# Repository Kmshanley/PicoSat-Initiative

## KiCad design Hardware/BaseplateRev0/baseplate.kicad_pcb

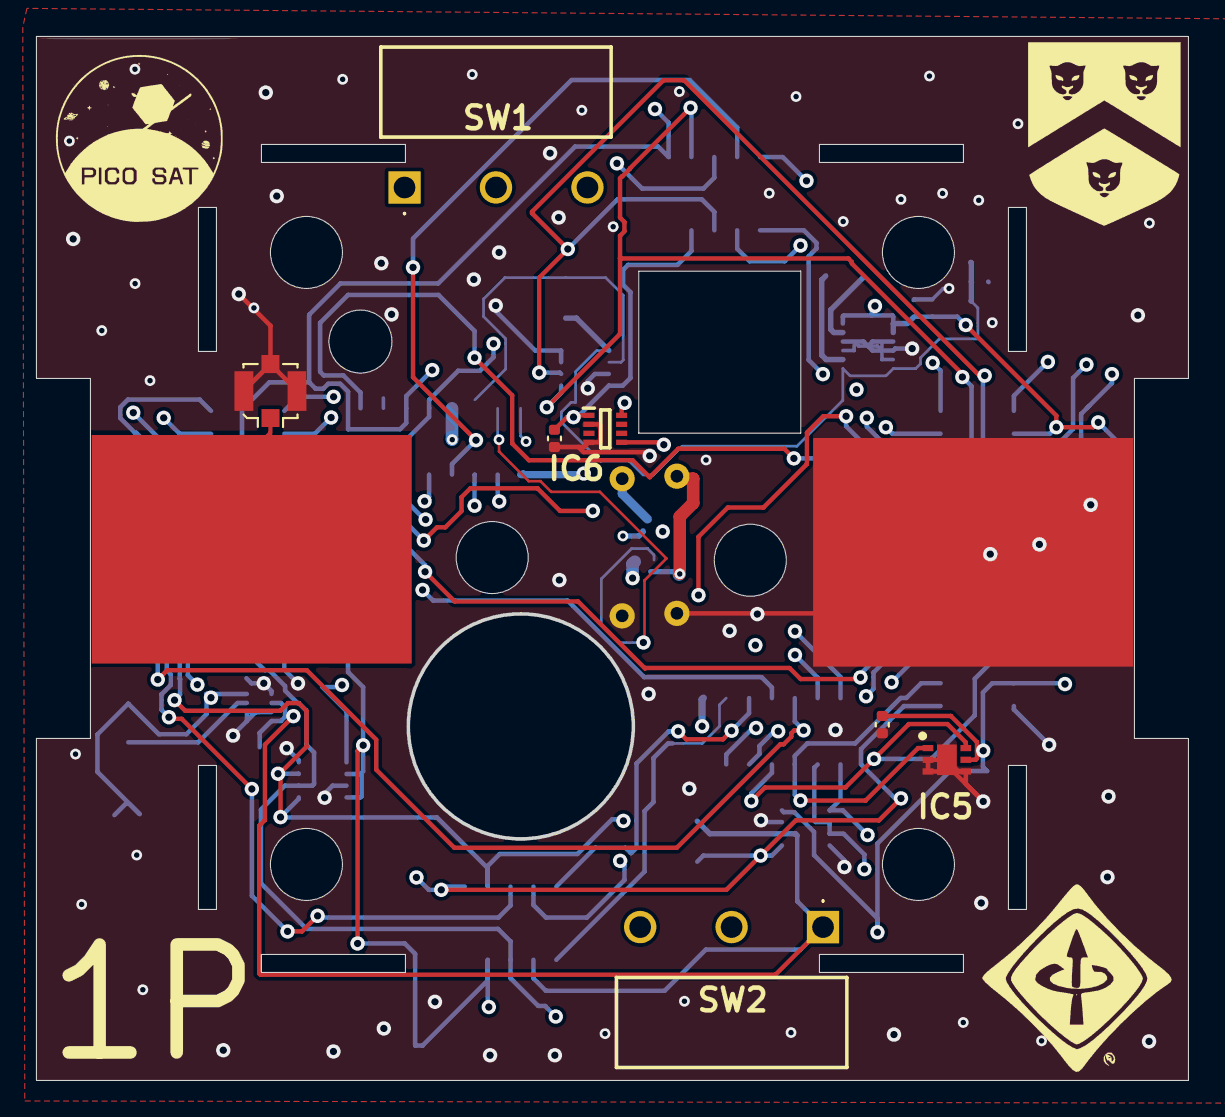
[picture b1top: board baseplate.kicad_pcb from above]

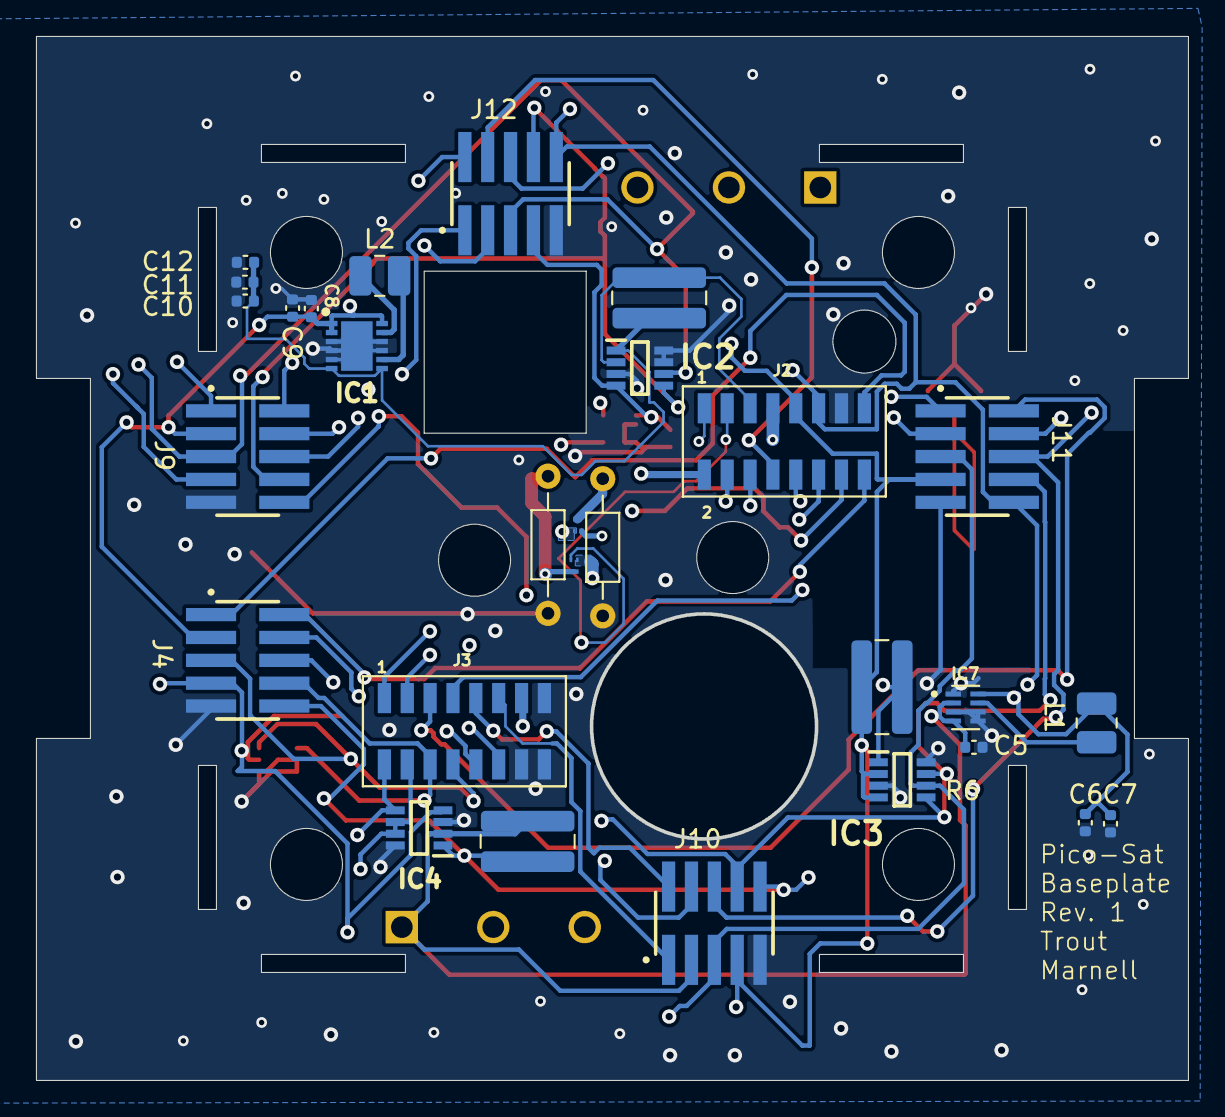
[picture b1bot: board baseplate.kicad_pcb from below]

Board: 4 copper layers, 64.0 x 58.0 mm, 38 parts (29 on the bottom side), 36 nets.

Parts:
C5: 4.7uF; C_0402_1005Metric
C6, C9, C10, C11: 10uF; C_0402_1005Metric
C7, C8, C12: 1uF; C_0402_1005Metric
C13, C14: 0.1uF; C_0402_1005Metric
IC1: RP604K331A-TR; SON50P270X300X60-13N
IC2, IC3, IC4: INA236AIDDFR; SOP65P280X110-8N
IC5: TMP117MAIDRVR; SON65P200X200X80-7N
IC6: OPT4048DTSR; SOTFL50P190X60-8N
IC7: TPS62840DLCR; SON50P200X150X100-8N
J1: Conn_Coaxial; U.FL_Molex_MCRF_73412-0110_Vertical
J2, J3: FLE-108-01-XX-DV
J4, J9, J10, J11, J12: FTSH-105-XX-X-DV; SAMTEC_FTSH-105-XX-X-DV
L1, L2: 2.2uH; L_1008_2520Metric
Q1, Q2: 2N7002; Transistor for baseplate
R1, R2: R_Small_US; R_Axial_DIN0204_L3.6mm_D1.6mm_P7.62mm_Horizontal
R5, R6, R7: 20m; R_1020_2550Metric
SW1, SW2: SW_SPDT; D2FL2A1
U1: (no value)
U2: antenna

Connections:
1.8V: C13.2, C14.2, IC2.4 (VS), IC3.2 (IN-), IC3.4 (VS), IC4.4 (VS), IC5.5 (V+), IC6.1 (VDD), J2.9, J4.07, J9.07, J10.07, J11.07, J12.07, R6.2
1V8 MEASURE: C6.1, C7.1, IC3.1 (IN+), IC7.8 (VOS), L1.2, R6.1
3.3V: IC2.2 (IN-), J2.5, R5.2
3V3 MEASURE: C10.1, C11.1, C12.1, IC1.6 (VFB), IC1.7 (VOUT), IC2.1 (IN+), R5.1
Battery +: C5.1, C8.2, C9.2, IC1.1 (AVIN), IC1.2 (CE), IC1.12 (PVIN), IC4.2 (IN-), IC7.2 (VIN), IC7.4 (EN), J2.2, J3.13, J4.03, J9.03, J10.03, J11.03, J12.03, Q1.2 (S), Q2.2 (S), R7.2, SW1.1 (A), SW2.1 (A)
DRV ENABLE 1: J2.14, J9.04
DRV ENABLE 2: J2.12, J10.04
DRV ENABLE 3: J2.10, J11.04
DRV ENABLE 4: J2.8, J12.04
DRV ENABLE 5: J2.6, J4.04
GND: C5.2, C6.2, C7.2, C8.1, C9.1, C10.2, C11.2, C12.2, C13.1, C14.1, IC1.3 (PGND_1), IC1.4 (PGND_2), IC1.5 (AGND), IC1.9 (PGND_3), IC1.10 (PGND_4), IC1.13 (EP), IC2.3 (GND), IC2.7 (A0), IC2.8 (ALERT), IC3.3 (GND), IC3.8 (ALERT), IC4.3 (GND), IC4.8 (ALERT), IC5.2 (GND), IC5.3 (ALERT), IC5.4 (ADD0), IC5.7 (EP), IC6.2 (ADDR), IC6.4 (GND), IC7.1 (GND), IC7.3 (MODE), IC7.5 (VSET), IC7.6 (STOP), J1.2 (Ext), J2.13, J3.14, J3.15, J3.16, J4.09, J9.09, J10.09, J11.09, J12.09, R1.2, R2.2, U1.1 (RF_IN)
MCU ENABLE 1: J2.3, Q1.1 (G)
MCU ENABLE 2: J2.1, Q2.1 (G)
MPPT ENABLE: J2.4, J4.06, J9.06, J10.06, J11.06, J12.06
unnamed: IC1.8 (BOLX), L2.2
unnamed: IC1.11 (BULX), L2.1
unnamed: IC7.7 (SW), L1.1
unnamed: Q2.3 (D), R1.1
unnamed: Q1.3 (D), R2.1
PWM1(1): J3.10, J9.01
PWM1(2): J3.11, J10.01
PWM1(3): J3.7, J11.01
PWM1(4): J3.3, J12.01
PWM1(5): J2.15, J4.01
PWM2(1): J3.12, J9.02
PWM2(2): J3.9, J10.02
PWM2(3): J3.5, J11.02
PWM2(4): J3.1, J12.02
PWM2(5): J2.16, J4.02
RF ANTENNA: J1.1 (In), U2.1 (RF_IN)
SCL(1): IC2.5 (SCL), IC3.5 (SCL), IC3.7 (A0), IC4.5 (SCL), J3.2, J9.08, J10.08, J11.08, J12.08
SCL(2): IC5.1 (SCL), IC6.5 (SCL), J3.6, J4.08
SDA(1): IC2.6 (SDA), IC3.6 (SDA), IC4.6 (SDA), IC4.7 (A0), J3.4, J9.05, J10.05, J11.05, J12.05
SDA(2): IC5.6 (SDA), IC6.8 (SDA), J3.8, J4.05
VBAT+: J2.7, SW1.2 (B), SW2.2 (B)
VMPPT: IC4.1 (IN+), J2.11, J4.10, J9.10, J10.10, J11.10, J12.10, R7.1

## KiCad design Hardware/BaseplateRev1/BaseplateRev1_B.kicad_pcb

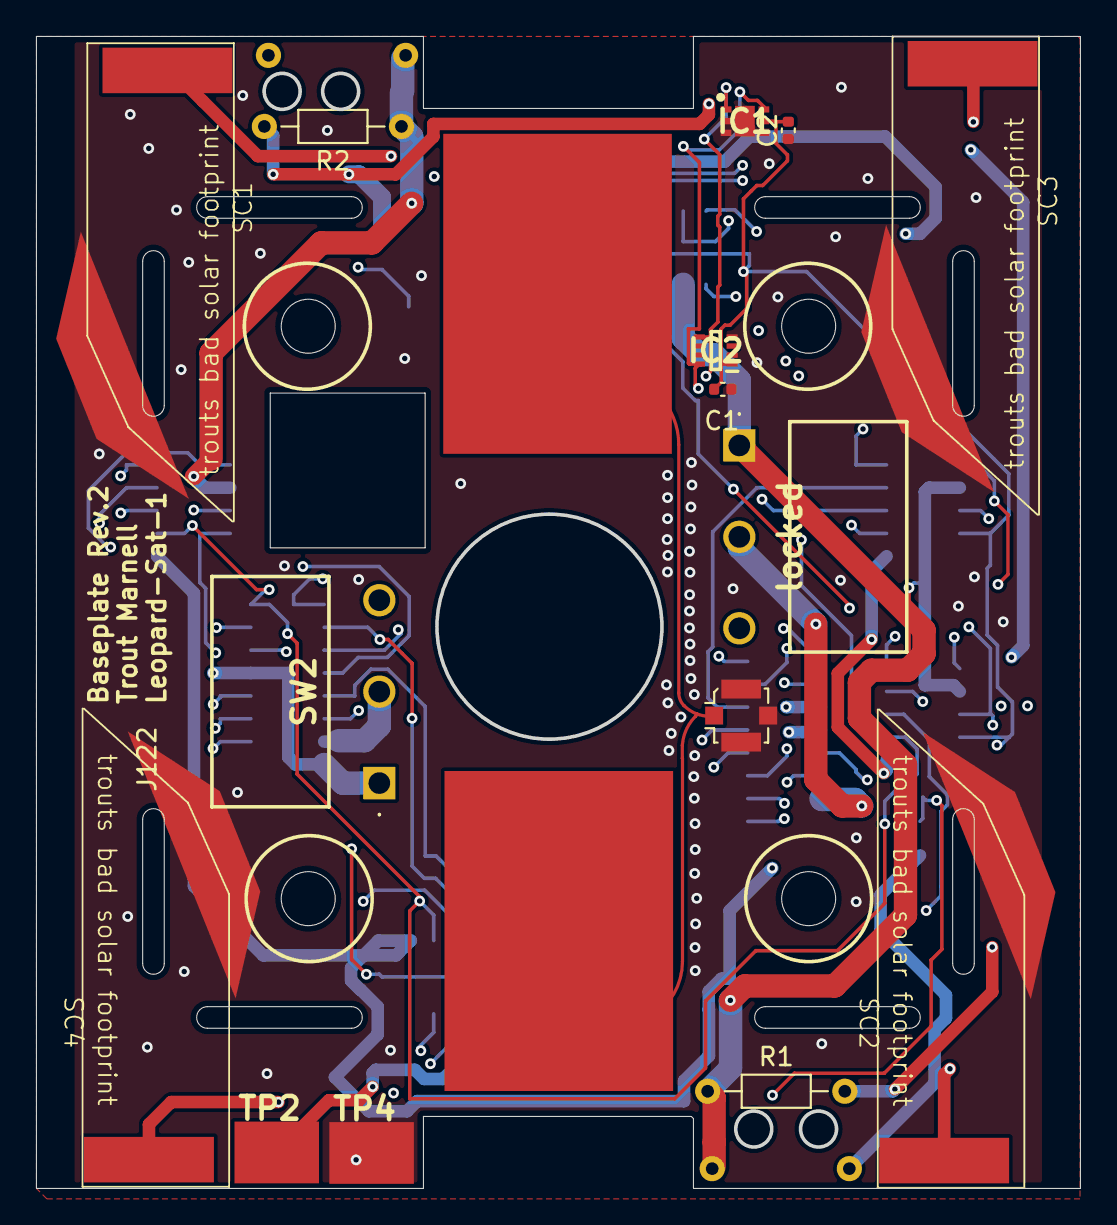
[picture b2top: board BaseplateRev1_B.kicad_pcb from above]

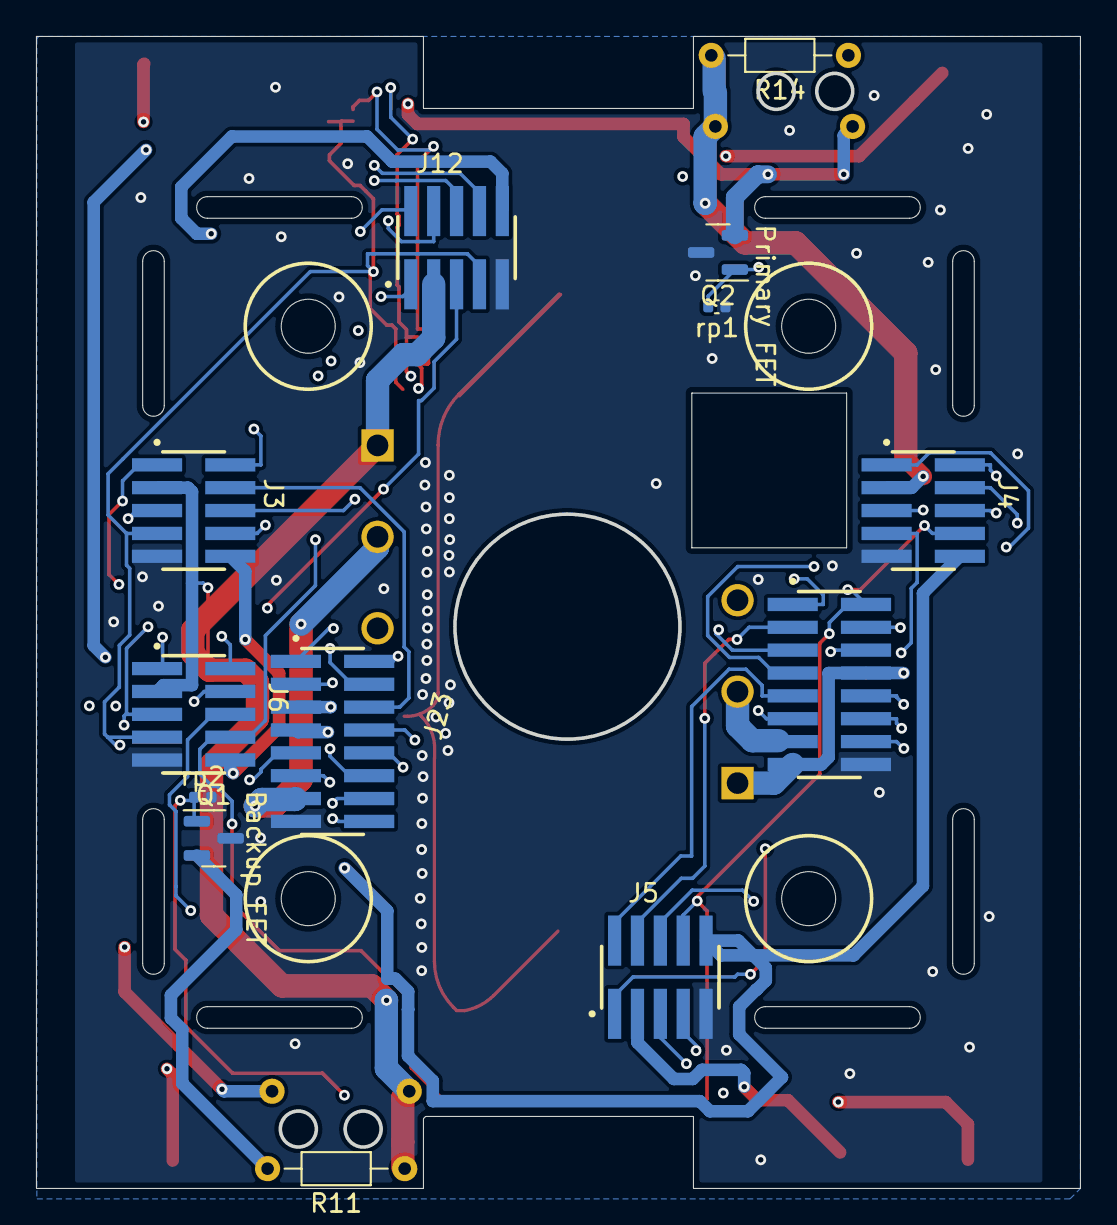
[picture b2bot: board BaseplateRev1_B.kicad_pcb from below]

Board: 4 copper layers, 58.0 x 64.0 mm, 30 parts (13 on the bottom side), 31 nets.

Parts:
C1, C2: 0.1uF; C_0402_1005Metric
IC1: TMP117MAIDRVR; SON65P200X200X80-7N
IC2: OPT4048DTSR; SOTFL50P190X60-8N
J3, J4, J5, J6, J12: FTSH-105-XX-X-DV; SAMTEC_FTSH-105-XX-X-DV
J8: Conn_Coaxial; U.FL_Molex_MCRF_73412-0110_Vertical
J23, J122: FLE-108-01-XX-DV; SAMTEC_FW-08-03-G-D-335-065
Q1, Q2: 2N7002; SOT-23
R1, R2, R11, R14: R_Small_US; R_Axial_DIN0204_L3.6mm_D1.6mm_P7.62mm_Horizontal
SC1, SC2, SC3, SC4: Solar_Cell; solar
SW2: SW_SPDT; D2FA1
TP2, TP4: TestPoint; 5016
U1, U2: antenna
locked: SW_SPDT; D2FA1
rp1, rp2: 100k; C_0402_1005Metric

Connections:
1.8V: C1.2, C2.2, IC1.5 (V+), IC2.1 (VDD), J3.07, J4.07, J5.07, J6.07, J12.07, J23.11, J122.14
Battery +: J3.03, J4.03, J5.03, J6.03, J12.03, J122.08, J122.15, R1.1, R2.1, R11.1, R14.2, SW2.1 (A), TP2.1, locked.1 (A)
DRV ENABLE 1: J4.04, J122.01
DRV ENABLE 2: J5.04, J122.03
DRV ENABLE 3: J6.04, J23.10
DRV ENABLE 4: J12.04, J23.08
DRV ENABLE 5: J3.04, J23.06
GND: C1.1, C2.1, IC1.2 (GND), IC1.3 (ALERT), IC1.4 (ADD0), IC1.7 (EP), IC2.2 (ADDR), IC2.4 (GND), J3.09, J4.09, J5.09, J6.09, J8.2 (Ext), J12.09, J23.15, J122.16, Q1.3 (D), Q2.3 (D), SC1.2 (-), SC2.2 (-), SC3.2 (-), SC4.2 (-), TP4.1, rp1.1, rp2.2
MCU ENABLE 1: J122.07, Q2.1 (G), rp1.2
MCU ENABLE 2: J122.05, Q1.1 (G), rp2.1
MPPT ENABLE: J3.06, J4.06, J5.06, J6.06, J12.06, J122.06
unnamed: Q1.2 (S), R11.2, R14.1
unnamed: Q2.2 (S), R1.2, R2.2
PWM1(1): J4.01, J122.10
PWM1(2): J5.01, J122.11
PWM1(3): J6.01, J23.02
PWM1(4): J12.01, J23.03
PWM1(5): J3.01, J23.09
PWM2(1): J4.02, J122.12
PWM2(2): J5.02, J122.09
PWM2(3): J6.02, J23.04
PWM2(4): J12.02, J23.01
PWM2(5): J3.02, J23.16
RF ANTENNA: J8.1 (In), U1.1 (RF_IN), U2.1 (RF_IN)
SCL(1): J4.08, J5.08, J6.08, J12.08, J122.02
SCL(2): IC1.1 (SCL), IC2.5 (SCL), J3.08, J23.12
SDA(1): J4.05, J5.05, J6.05, J12.05, J122.04
SDA(2): IC1.6 (SDA), IC2.8 (SDA), J3.05, J23.14
VBAT+: J23.13, J122.13, SW2.2 (B), locked.2 (B)
VMPPT: J3.10, J4.10, J5.10, J6.10, J12.10, J23.07
Vsolar: J23.05, SC1.1 (+), SC2.1 (+), SC3.1 (+), SC4.1 (+)

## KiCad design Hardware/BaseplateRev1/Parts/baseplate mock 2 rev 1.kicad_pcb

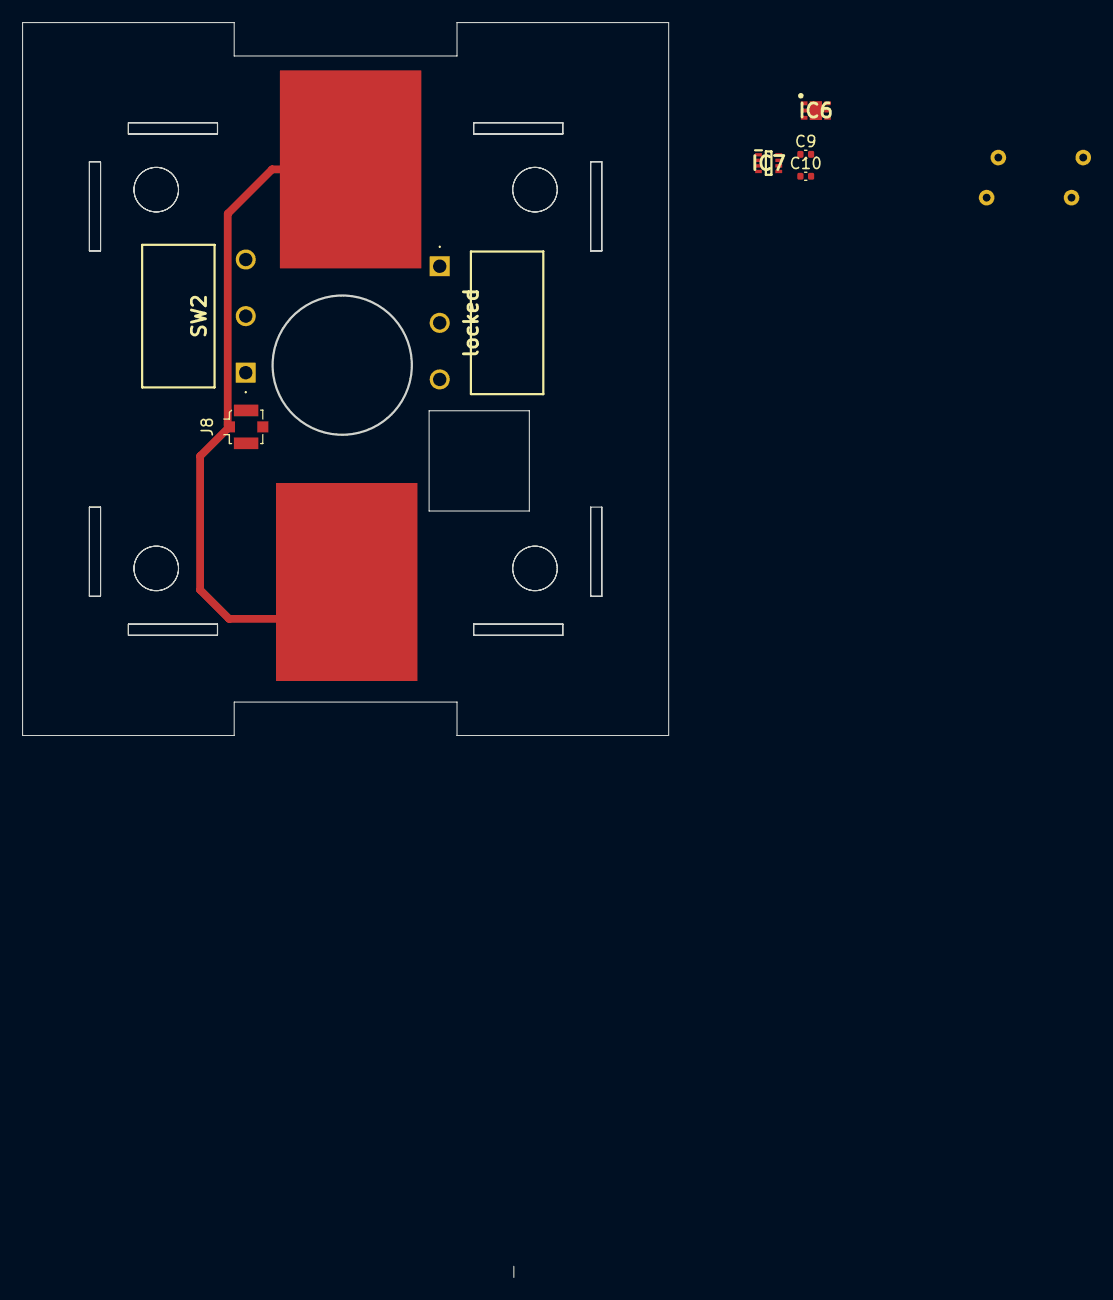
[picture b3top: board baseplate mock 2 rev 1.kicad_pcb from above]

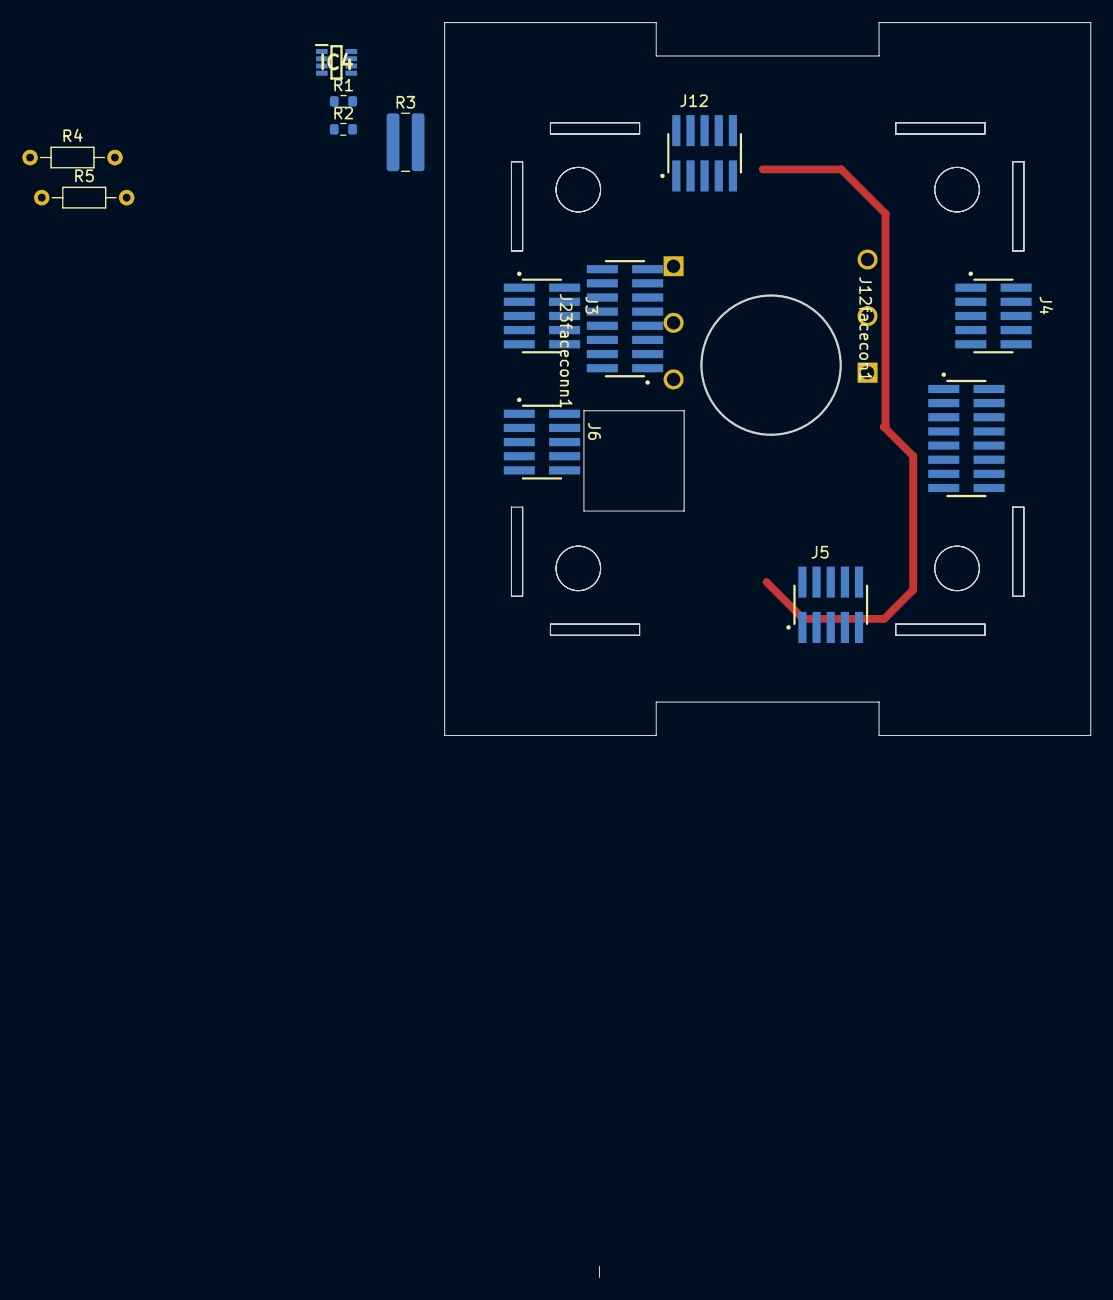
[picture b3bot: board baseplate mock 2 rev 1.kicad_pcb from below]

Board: 2 copper layers, 22 parts (13 on the bottom side), 29 nets.

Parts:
C9, C10: 0.1uF; C_0402_1005Metric
IC4: INA236AIDDFR; SOP65P280X110-8N
IC6: TMP117MAIDRVR; SON65P200X200X80-7N
IC7: OPT4048DTSR; SOTFL50P190X60-8N
J3, J4, J5, J6, J12: FTSH-105-XX-X-DV; SAMTEC_FTSH-105-XX-X-DV
J8: Conn_Coaxial; U.FL_Molex_MCRF_73412-0110_Vertical
J12facecon1, J23faceconn1: FLE-108-01-XX-DV; SAMTEC_FW-08-03-G-D-335-065
R1, R2: R_Small_US; R_0603_1608Metric
R3: 20m; R_1020_2550Metric
R4, R5: R_Small_US; R_Axial_DIN0204_L3.6mm_D1.6mm_P7.62mm_Horizontal
SW2: SW_SPDT; D2FA1
U2, U2#2: antenna
locked: SW_SPDT; D2FA1

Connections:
1.8V: J3.07, J4.07, J5.07, J6.07, J12.07, J12facecon1.14, J23faceconn1.11
+1V8: C9.2, C10.2, IC4.4 (VS), IC6.5 (V+), IC7.1 (VDD)
Battery +: IC4.2 (IN-), J3.03, J4.03, J5.03, J6.03, J12.03, J12facecon1.08, J12facecon1.13, R3.2, SW2.1 (A), locked.1 (A)
DRV ENABLE 1: J4.04, J12facecon1.01
DRV ENABLE 2: J5.04, J12facecon1.03
DRV ENABLE 3: J6.04, J23faceconn1.10
DRV ENABLE 4: J12.04, J23faceconn1.08
DRV ENABLE 5: J3.04, J23faceconn1.06
GND: C9.1, C10.1, IC4.3 (GND), IC4.7 (A0), IC4.8 (ALERT), IC6.2 (GND), IC6.3 (ALERT), IC6.4 (ADD0), IC6.7 (EP), IC7.2 (ADDR), IC7.4 (GND), J3.09, J4.09, J5.09, J6.09, J8.2 (Ext), J12.09, J12facecon1.15, J12facecon1.16, J23faceconn1.13, J23faceconn1.15, R4.2, R5.2
MCU ENABLE 1: J12facecon1.07, R2.1
MCU ENABLE 2: J12facecon1.05, R1.1
MPPT ENABLE: J3.06, J4.06, J5.06, J6.06, J12.06, J12facecon1.06
PWM1(1): J4.01, J12facecon1.10
PWM1(2): J5.01, J12facecon1.11
PWM1(3): J6.01, J23faceconn1.02
PWM1(4): J12.01, J23faceconn1.03
PWM1(5): J3.01, J23faceconn1.09
PWM2(1): J4.02, J12facecon1.12
PWM2(2): J5.02, J12facecon1.09
PWM2(3): J6.02, J23faceconn1.04
PWM2(4): J12.02, J23faceconn1.01
PWM2(5): J3.02, J23faceconn1.16
RF ANTENNA: J8.1 (In), U2.1 (RF_IN), U2#2.1 (RF_IN)
SCL(1): IC4.5 (SCL), J4.08, J5.08, J6.08, J12.08, J12facecon1.02
SCL(2): IC6.1 (SCL), IC7.5 (SCL), J3.08, J23faceconn1.12
SDA(1): IC4.6 (SDA), J4.05, J5.05, J6.05, J12.05, J12facecon1.04
SDA(2): IC7.8 (SDA), J3.05, J23faceconn1.14
VBAT+: J23faceconn1.05, SW2.2 (B), locked.2 (B)
VMPPT: IC4.1 (IN+), J3.10, J4.10, J5.10, J6.10, J12.10, J23faceconn1.07, R3.1

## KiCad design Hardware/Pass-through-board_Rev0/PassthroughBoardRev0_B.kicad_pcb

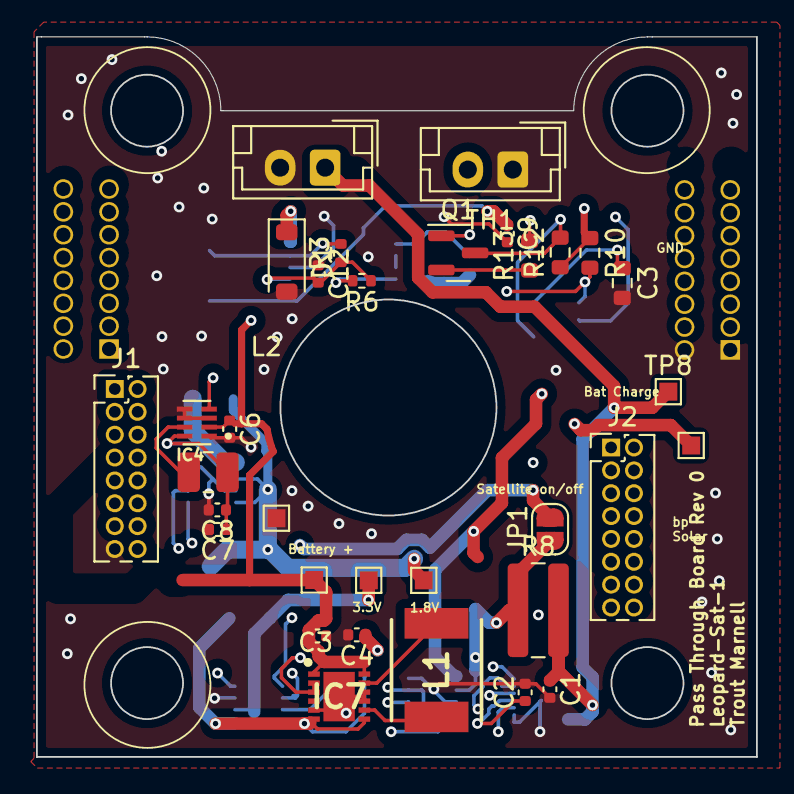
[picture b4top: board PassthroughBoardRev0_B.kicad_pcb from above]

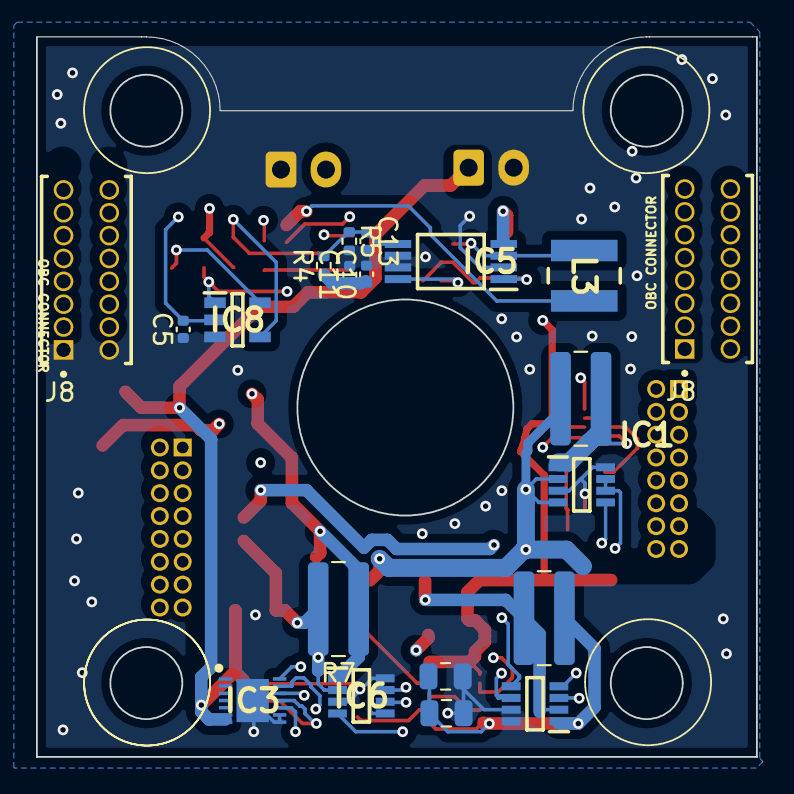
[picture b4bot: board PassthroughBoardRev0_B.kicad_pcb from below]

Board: 4 copper layers, 40.0 x 40.0 mm, 53 parts (20 on the bottom side), 26 nets.

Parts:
C1: .1uF; C_0402_1005Metric
C2: .47uF; C_0402_1005Metric
C3: 10uF; R_0603_1608Metric
C3#2, C7, C9, C10: 10uF; C_0402_1005Metric
C4: 22uF; C_0402_1005Metric
C5, C8: 1uF; C_0402_1005Metric
C6, C11: 4.7uF; C_0402_1005Metric
C12: 100nF; C_0402_1005Metric
C13: 1nF; C_0402_1005Metric
D1: 4.5v; D_SOD-123
IC1, IC2, IC6: INA236AIDDFR; SOP65P280X110-8N
IC3: MAX17260SETD+T; SON40P300X300X80-15N
IC4: TPS62840DLCR; SON50P200X150X100-8N
IC5: SPV1040T; SOP65P640X120-8N
IC7: RP602K330G-TR; SON50P270X300X60-13N
IC8: TLV840MADL30DBVRQ1; SOT95P280X145-5N
J1, J2: FLE-108-01-XX-DV; PinHeader_2x08_P1.27mm_Vertical
J3: Conn_01x02_Socket; JST_EH_B2B-EH-A_1x02_P2.50mm_Vertical
J8, J8#2: SLM-108-01-L-D; SAMTEC_SLM-108-01-L-D
JP1: SolderJumper_2_Open; SolderJumper-2_P1.3mm_Open_RoundedPad1.0x1.5mm
L1: 1.0uH; INDPM5650X530N
L2: 2.2uH; L_1008_2520Metric
L3: NRS4012T150MDGJ
Q1: 2N7002; SOT-23
R1, R2, R7: 20m; R_1020_2550Metric
R3: 1K; R_0402_1005Metric
R4, R6: 1M; R_0402_1005Metric
R5: 420k; R_0402_1005Metric
R8: 10m; R_1020_2550Metric
R10, R12: 1M; R_0603_1608Metric
R13: 5k; R_0603_1608Metric
TH1: Thermistor_NTC 10k; JST_EH_B2B-EH-A_1x02_P2.50mm_Vertical
TP1, TP2, TP3, TP4, TP6, TP8: TestPoint_Alt; TestPoint_Pad_1.0x1.0mm
ff: C_0805_2012Metric
gg: C_0805_2012Metric

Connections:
1.8V: IC1.4 (VS), IC2.2 (IN-), IC2.4 (VS), IC6.4 (VS), J1.13, J2.5, Q1.1 (G), R2.2, R13.2, TP3.1
1V8 MEASURE: C7.1, C8.1, IC2.1 (IN+), IC4.8 (VOS), L2.2, R2.1
3.3V: C5.2, IC1.2 (IN-), IC8.2 (VDD), R1.2, TP2.1
3V3 MEASURE: C4.1, IC1.1 (IN+), IC7.6 (VFB), IC7.7 (VOUT), R1.1, ff.1, gg.1
Battery +: C3#2.2, C6.1, IC4.2 (VIN), IC7.1 (AVIN), IC7.12 (PVIN), J1.7, J1.16, R10.1, R12.1, TP1.1
Battery Charge: C1.1, IC3.6 (BATT), IC3.7 (CSN), J3.1, R8.2, TP8.1
CONV_SHUTDOWN: IC4.4 (EN), IC7.2 (CE), IC7.3 (MODE), IC8.1 (~RESET_/_RESET), R10.2
CT: C3.1, IC8.5 (CT)
GND: C1.2, C2.2, C3.2, C3#2.1, C4.2, C5.1, C6.2, C7.2, C8.2, C9.2, C10.2, C11.2, C12.1, C13.2, D1.2 (A), IC1.3 (GND), IC1.7 (A0), IC1.8 (ALERT), IC2.3 (GND), IC2.8 (ALERT), IC3.8 (GND), IC3.9 (CSPL), IC3.15 (EP), IC4.1 (GND), IC4.3 (MODE), IC4.5 (VSET), IC4.6 (STOP), IC5.2 (GND), IC5.6 (ICTRL_MINUS), IC5.7 (ICTRL_PLUS), IC6.3 (GND), IC6.8 (ALERT), IC7.5 (AGND), IC7.9 (PGND_1), IC7.10 (PGND_2), IC7.13 (GROUND), IC8.3 (GND), J1.15, J2.1, J3.2, R5.2, TH1.1, TP4.1, ff.2, gg.2
MPPT ENABLE: IC5.8 (XSHUT), R6.2
unnamed: C2.1, IC3.11 (REG)
unnamed: IC3.1 (TH), TH1.2
unnamed: IC4.7 (SW), L2.1
unnamed: IC5.3 (LX), L3.1, R3.2
unnamed: C12.2, IC5.1 (MPP-SET), R3.1, R6.1
unnamed: C13.1, IC5.5 (VCTRL), R4.2, R5.1
unnamed: IC7.8 (BOLX), L1.2
unnamed: IC7.11 (BULX), L1.1
unnamed: IC8.4 (~MR), Q1.3 (D), R12.2
SAT_REST: Q1.2 (S), R13.1
SCL(1): IC1.5 (SCL), IC2.5 (SCL), IC3.14 (SCL), IC6.5 (SCL), IC6.7 (A0), J1.1
SDA(1): IC1.6 (SDA), IC2.6 (SDA), IC2.7 (A0), IC3.13 (SDA), IC6.6 (SDA), J1.3
VBAT+: J1.14, J2.3, JP1.2 (B)
VMPPT: C10.1, C11.1, D1.1 (K), IC5.4 (VOUT), IC6.1 (IN+), J2.9, R4.1, R7.1
VMPPTCHARGE: IC3.10 (CSPH), IC6.2 (IN-), JP1.1 (A), R7.2, R8.1
Vsolar: C9.1, J2.11, L3.2, TP6.1
